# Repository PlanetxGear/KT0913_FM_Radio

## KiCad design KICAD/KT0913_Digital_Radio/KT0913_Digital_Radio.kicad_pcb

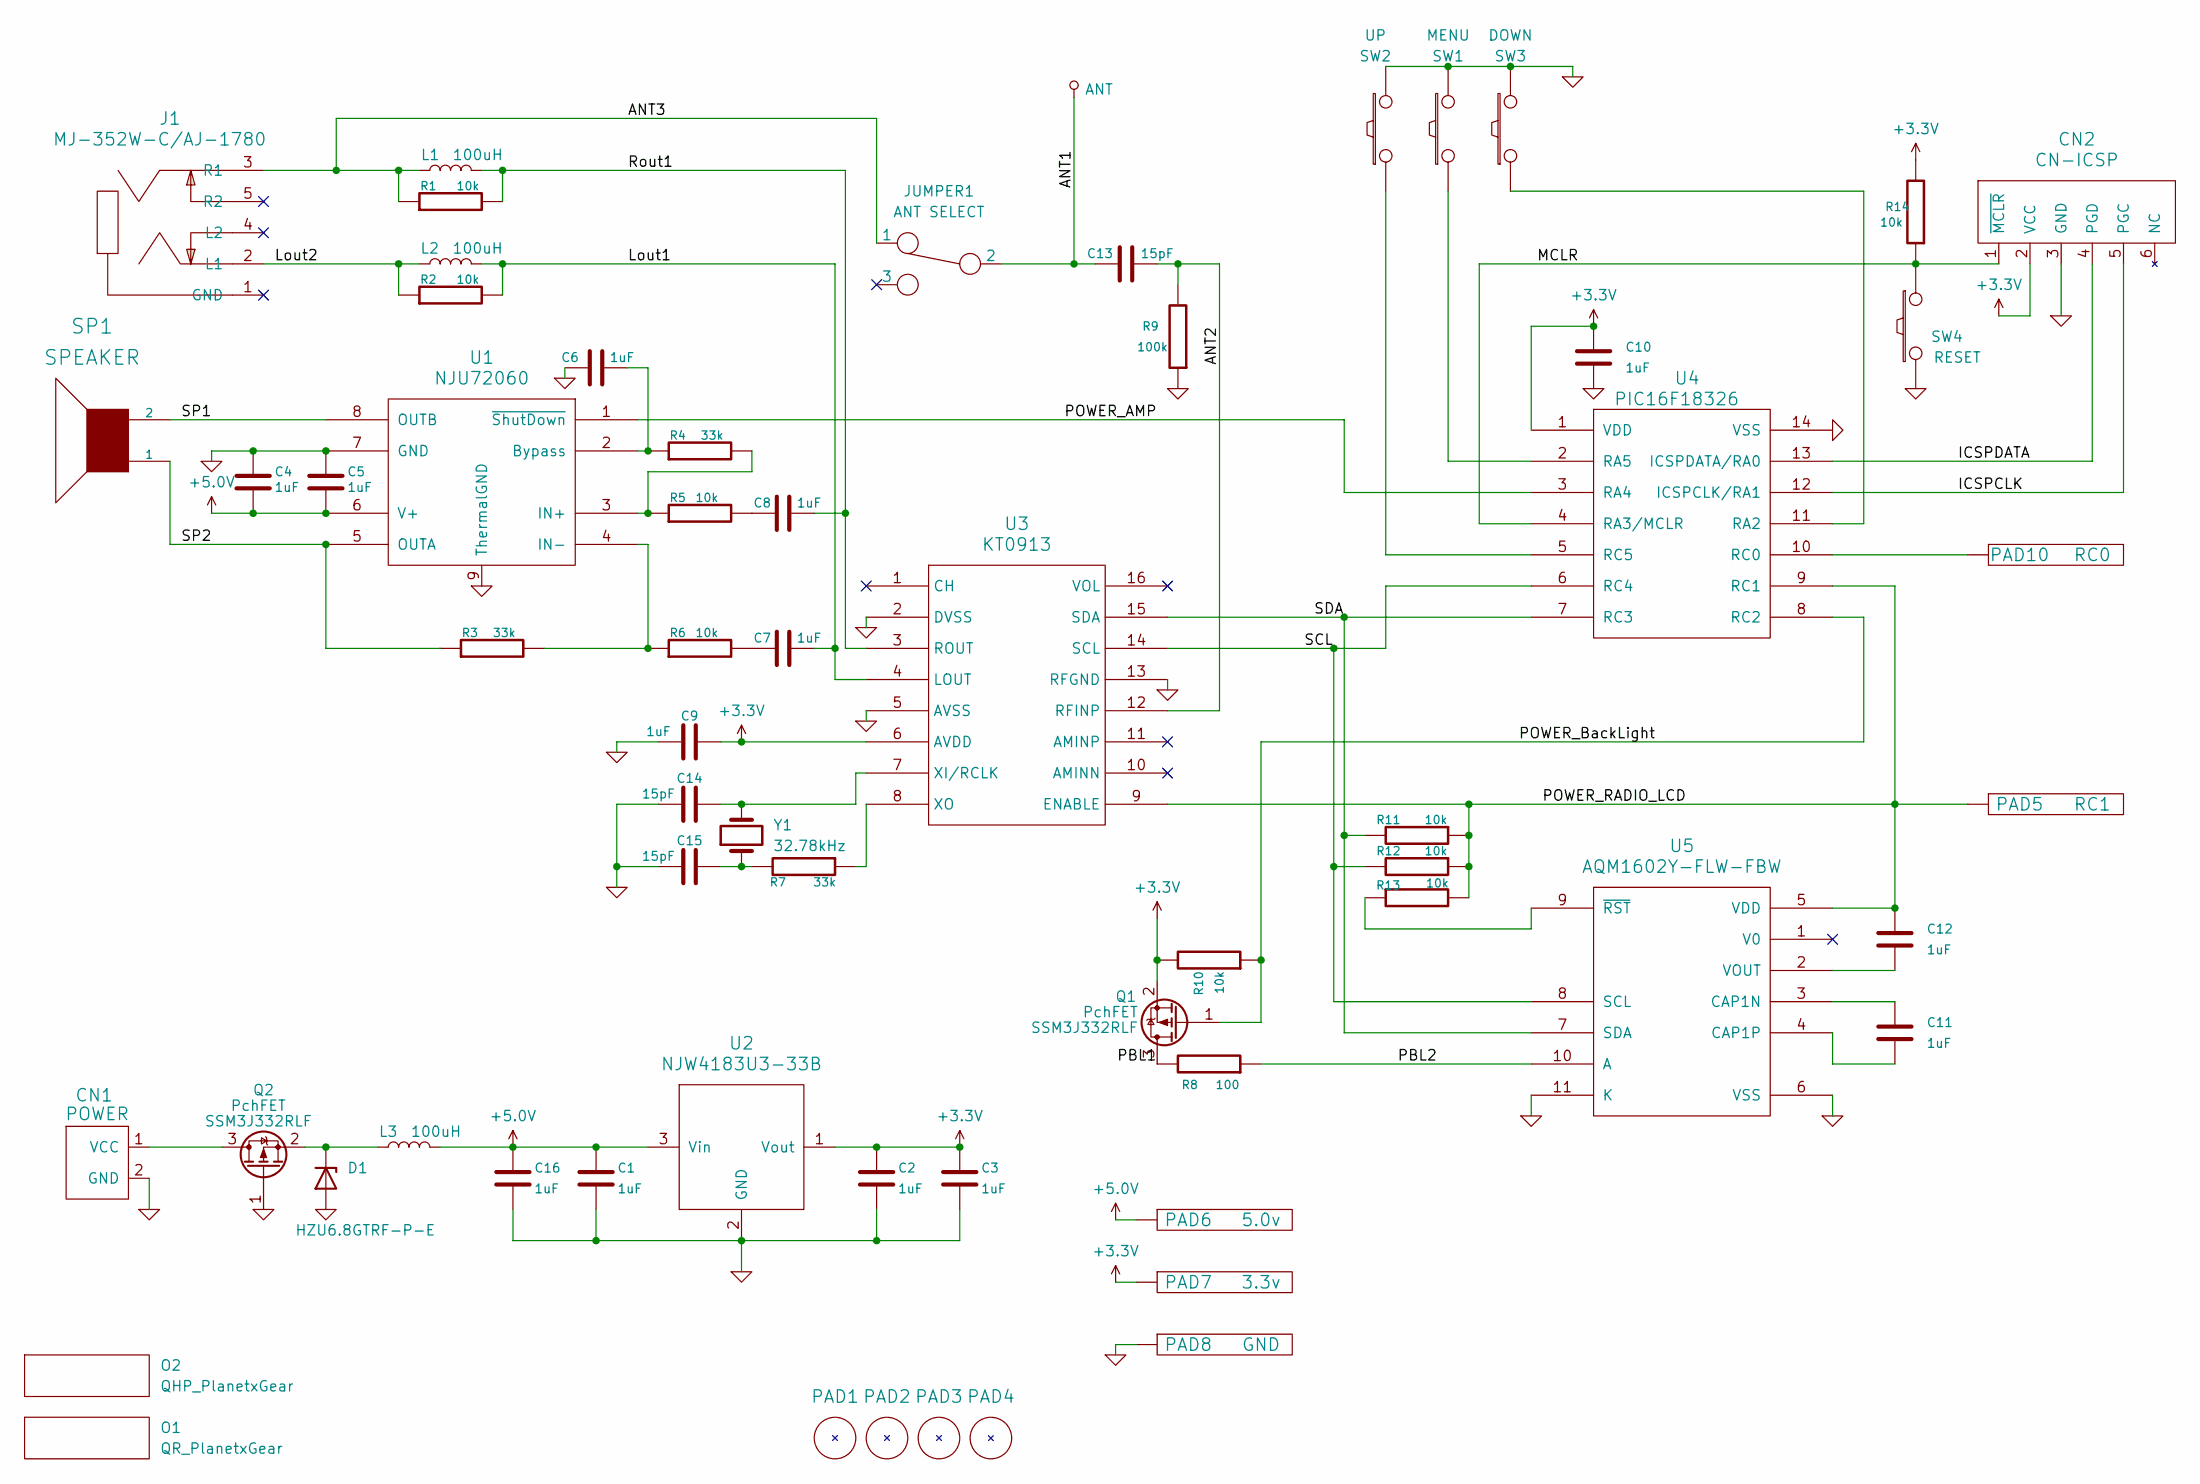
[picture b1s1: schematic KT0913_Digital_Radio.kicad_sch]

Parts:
ANT1: ANT; PAD1mmX2m
C1, C2, C3, C4, C5, C6, C7, C8, C9, C10, C11, C12, C16: 1uF; SMD_0603_1608_MU_HandSolder
C13, C14, C15: 15pF; C2_MU5mm
CN1: POWER; TERMINAL_2P_POWER
CN2: CN-ICSP; PINHEAD1-PICkit_ICSP_Tin
D1: HZU6.8GTRF-P-E; SC-76A
J1: MJ-352W-C/AJ-1780; JACK_EarPhone_MJ-352W-C_R
JUMPER1: ANT SELECT; JUMPER1-3
L1, L2: 100uH; L4_MU9mm
L3: 100uH; L4_MU10mm
O1: QR_PlanetxGear
O2: QHP_PlanetxGear
PAD1, PAD2, PAD3, PAD4: PAD; PAD3mmX5mm
PAD5: RC1; PAD1mmX2m
PAD6: 5.0v; PAD1mmX2m
PAD7: 3.3v; PAD1mmX2m
PAD8: GND; PAD1mmX2m
PAD10: RC0; PAD1mmX2m
Q1, Q2: SSM3J332RLF; SOT-23-3_MU_Handsoldering
R1, R2, R5, R6, R10, R11, R12, R13, R14: 10k; SMD_0603_1608_MU_HandSolder
R3, R4, R7: 33k; R4_MU8mm
R8: 100; R4_MU8mm
R9: 100k; R4_MU8mm
SP1: SPEAKER; TERMINAL_2P
SW1: MENU; SW_PUSH-6mm_AK
SW2: UP; SW_PUSH-6mm_AK
SW3: DOWN; SW_PUSH-6mm_AK
SW4: RESET; SW_PUSH_TVAF06-A020B-R
U1: NJU72060; SOP-8_6x5mm_P1.27mm_EP3.0x4.4mm_ThermalVias
U2: NJW4183U3-33B; SOT-89-3_MU_Handsoldering
U3: KT0913; SSOP-16_MU_3.9x4.9mm_P0.635mm
U4: PIC16F18326; DIP-14_300_MU
U5: AQM1602Y-FLW-FBW; LCD_AQM1602Y-FLW-FBW
Y1: 32.78kHz; X_TAL_VT200

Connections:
+3.3V: C2.1, C3.1, C9.2, C10.1, CN2.2 (VCC), PAD7.1, Q1.2 (S), R10.2, R14.2, U2.1 (Vout), U3.6 (AVDD), U4.1 (VDD)
+5.0V: C1.1, C4.2, C5.2, C16.1, L3.2, PAD6.1, U1.6 (V+), U2.3 (Vin)
/ANT1: ANT1.1 (ANT), C13.2, JUMPER1.2
/ANT2: C13.1, R9.2, U3.12 (RFINP)
/ANT3: J1.3 (R1), JUMPER1.1, L1.1, R1.1
/ICSPCLK: CN2.5 (PGC), U4.12 (ICSPCLK/RA1)
/ICSPDATA: CN2.4 (PGD), U4.13 (ICSPDATA/RA0)
/Lout1: C7.1, L2.2, R2.2, U3.4 (LOUT)
/Lout2: J1.2 (L1), L2.1, R2.1
/MCLR: CN2.1 (~MCLR), R14.1, SW4.1, U4.4 (RA3/MCLR)
/PBL1: Q1.3 (D), R8.2
/PBL2: R8.1, U5.10 (A)
/POWER_AMP: U1.1 (~ShutDown), U4.3 (RA4)
/POWER_BackLight: Q1.1 (G), R10.1, U4.8 (RC2)
/POWER_RADIO_LCD: C12.1, PAD5.1, R11.1, R12.1, R13.2, U3.9 (ENABLE), U4.9 (RC1), U5.5 (VDD)
/Rout1: C8.1, L1.2, R1.2, U3.3 (ROUT)
/SCL: R12.2, U3.14 (SCL), U4.6 (RC4), U5.8 (SCL)
/SDA: R11.2, U3.15 (SDA), U4.7 (RC3), U5.7 (SDA)
/SP1: SP1.2, U1.8 (OUTB)
/SP2: R3.1, SP1.1, U1.5 (OUTA)
GND: C1.2, C2.2, C3.2, C4.1, C5.1, C6.2, C9.1, C10.2, C14.1, C15.1, C16.2, CN1.2 (GND), CN2.3 (GND), D1.2 (A), PAD8.1, Q2.1 (G), R9.1, SW1.2, SW2.2, SW3.2, SW4.2, U1.7 (GND), U1.9 (ThermalGND), U2.2 (GND), U3.2 (DVSS), U3.5 (AVSS), U3.13 (RFGND), U4.14 (VSS), U5.6 (VSS), U5.11 (K)
unnamed: C7.2, R6.2
unnamed: C8.2, R5.2
unnamed: C15.2, R7.2, Y1.1
unnamed: CN1.1 (VCC), Q2.3 (D)
unnamed: D1.1 (K), L3.1, Q2.2 (S)
unnamed: PAD10.1, U4.10 (RC0)
unnamed: C6.1, R4.1, U1.2 (Bypass)
unnamed: R4.2, R5.1, U1.3 (IN+)
unnamed: R3.2, R6.1, U1.4 (IN-)
unnamed: C14.2, U3.7 (XI/RCLK), Y1.2
unnamed: R7.1, U3.8 (XO)
unnamed: SW3.1, U4.11 (RA2)
unnamed: SW1.1, U4.2 (RA5)
unnamed: SW2.1, U4.5 (RC5)
unnamed: C11.1, U5.3 (CAP1N)
unnamed: C11.2, U5.4 (CAP1P)
unnamed: C12.2, U5.2 (VOUT)
unnamed: R13.1, U5.9 (~RST)

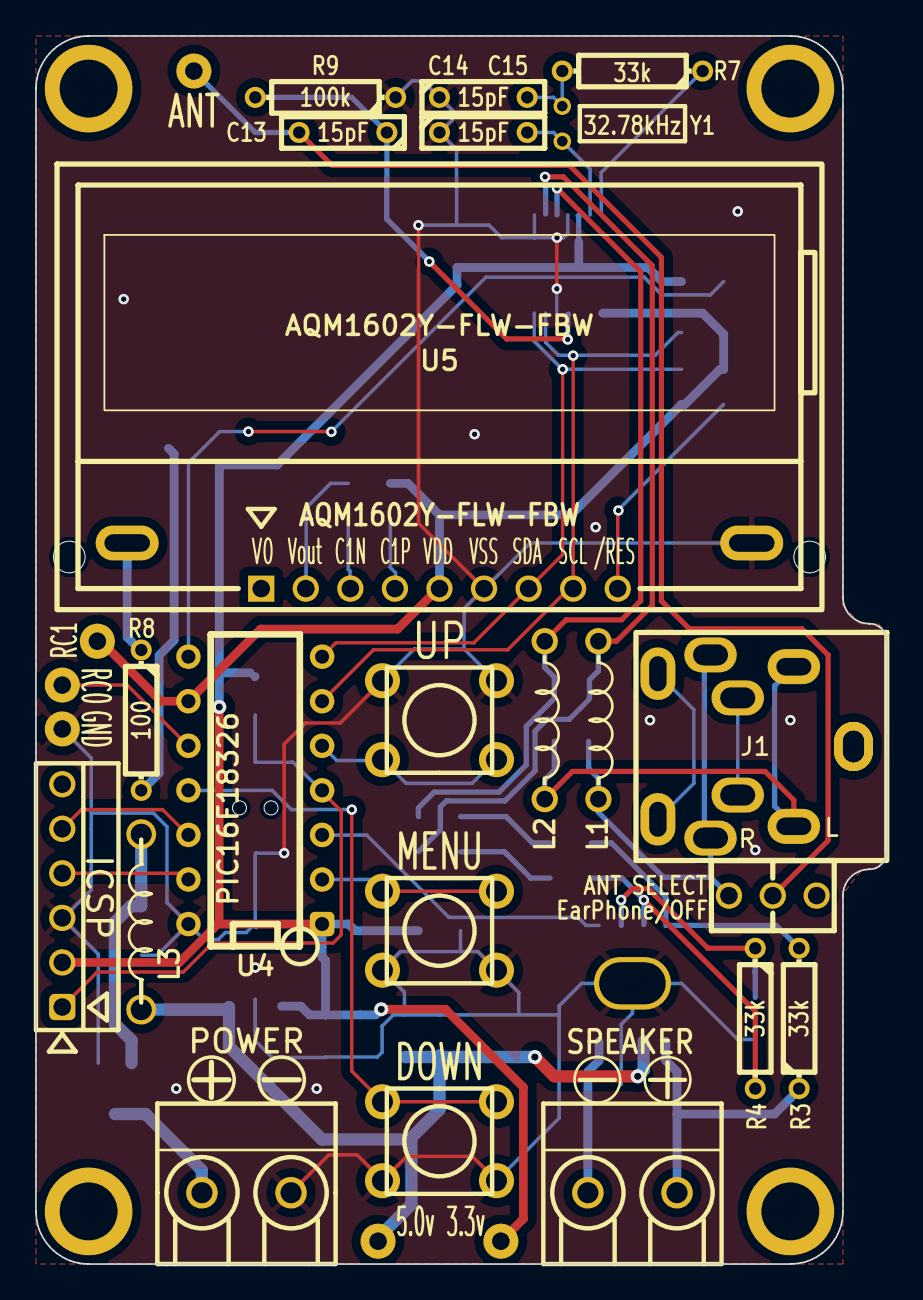
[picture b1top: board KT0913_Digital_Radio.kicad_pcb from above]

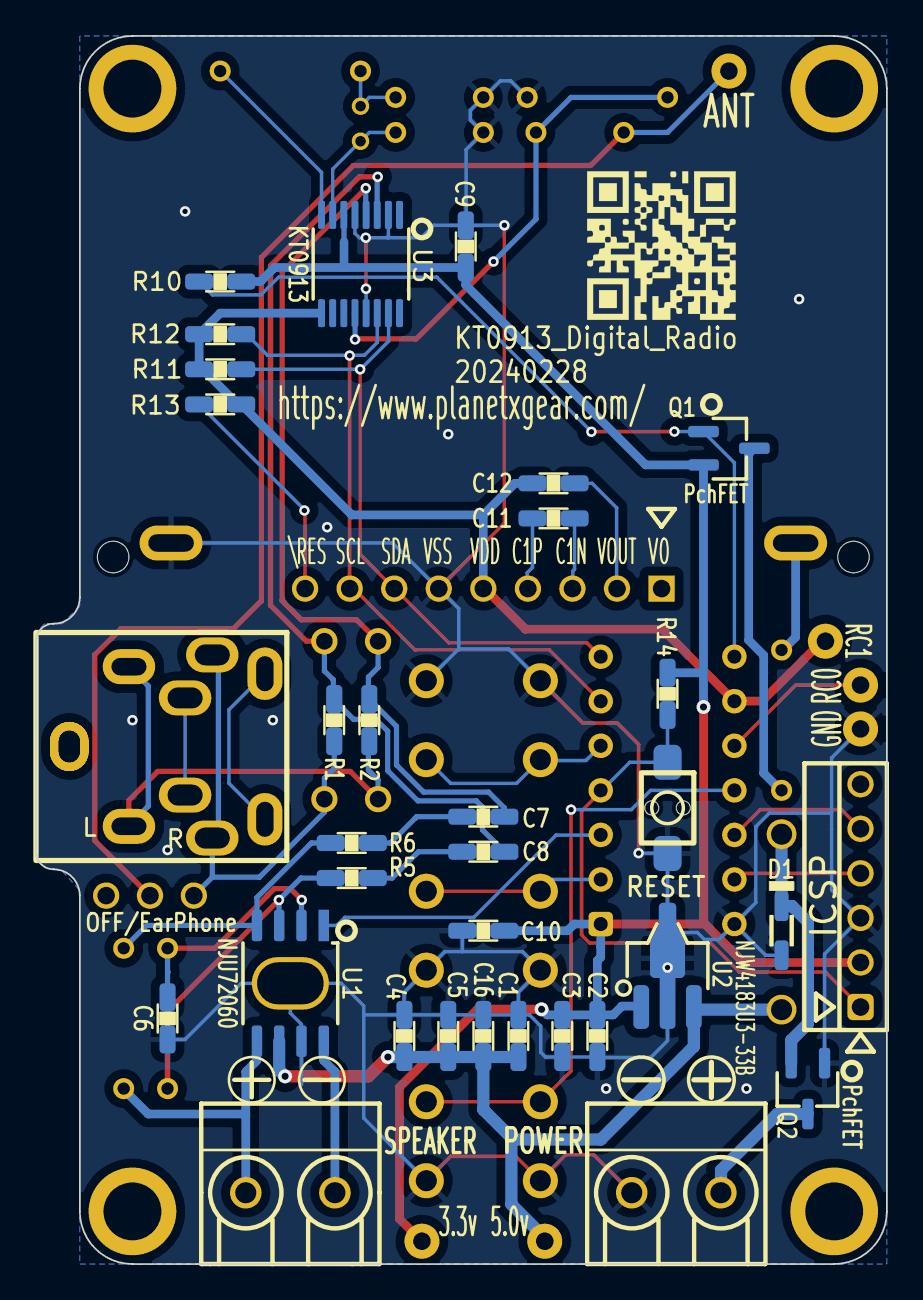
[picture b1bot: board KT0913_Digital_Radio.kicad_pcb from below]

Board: 2 copper layers, 48.5 x 70.0 mm, 63 parts (32 on the bottom side), 39 nets.

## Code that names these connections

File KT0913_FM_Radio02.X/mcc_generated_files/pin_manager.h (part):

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// get/set IO_RA0_NC aliases
#define IO_RA0_NC_TRIS                 TRISAbits.TRISA0
#define IO_RA0_NC_LAT                  LATAbits.LATA0
#define IO_RA0_NC_PORT                 PORTAbits.RA0
#define IO_RA0_NC_WPU                  WPUAbits.WPUA0
#define IO_RA0_NC_OD                   ODCONAbits.ODCA0
#define IO_RA0_NC_ANS                  ANSELAbits.ANSA0
#define IO_RA0_NC_SetHigh()            do { LATAbits.LATA0 = 1; } while(0)
#define IO_RA0_NC_SetLow()             do { LATAbits.LATA0 = 0; } while(0)
#define IO_RA0_NC_Toggle()             do { LATAbits.LATA0 = ~LATAbits.LATA0; } while(0)
#define IO_RA0_NC_GetValue()           PORTAbits.RA0
#define IO_RA0_NC_SetDigitalInput()    do { TRISAbits.TRISA0 = 1; } while(0)
#define IO_RA0_NC_SetDigitalOutput()   do { TRISAbits.TRISA0 = 0; } while(0)
#define IO_RA0_NC_SetPullup()          do { WPUAbits.WPUA0 = 1; } while(0)
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// get/set IO_RA1_NC aliases
#define IO_RA1_NC_TRIS                 TRISAbits.TRISA1
#define IO_RA1_NC_LAT                  LATAbits.LATA1
#define IO_RA1_NC_PORT                 PORTAbits.RA1
#define IO_RA1_NC_WPU                  WPUAbits.WPUA1
#define IO_RA1_NC_OD                   ODCONAbits.ODCA1
#define IO_RA1_NC_ANS                  ANSELAbits.ANSA1
#define IO_RA1_NC_SetHigh()            do { LATAbits.LATA1 = 1; } while(0)
#define IO_RA1_NC_SetLow()             do { LATAbits.LATA1 = 0; } while(0)
#define IO_RA1_NC_Toggle()             do { LATAbits.LATA1 = ~LATAbits.LATA1; } while(0)
#define IO_RA1_NC_GetValue()           PORTAbits.RA1
#define IO_RA1_NC_SetDigitalInput()    do { TRISAbits.TRISA1 = 1; } while(0)
#define IO_RA1_NC_SetDigitalOutput()   do { TRISAbits.TRISA1 = 0; } while(0)
#define IO_RA1_NC_SetPullup()          do { WPUAbits.WPUA1 = 1; } while(0)
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// get/set SW3_down aliases
#define SW3_down_TRIS                 TRISAbits.TRISA2
#define SW3_down_LAT                  LATAbits.LATA2
#define SW3_down_PORT                 PORTAbits.RA2
#define SW3_down_WPU                  WPUAbits.WPUA2
#define SW3_down_OD                   ODCONAbits.ODCA2
#define SW3_down_ANS                  ANSELAbits.ANSA2
#define SW3_down_SetHigh()            do { LATAbits.LATA2 = 1; } while(0)
#define SW3_down_SetLow()             do { LATAbits.LATA2 = 0; } while(0)
#define SW3_down_Toggle()             do { LATAbits.LATA2 = ~LATAbits.LATA2; } while(0)
#define SW3_down_GetValue()           PORTAbits.RA2
#define SW3_down_SetDigitalInput()    do { TRISAbits.TRISA2 = 1; } while(0)
#define SW3_down_SetDigitalOutput()   do { TRISAbits.TRISA2 = 0; } while(0)
#define SW3_down_SetPullup()          do { WPUAbits.WPUA2 = 1; } while(0)
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// get/set POWER_AMP aliases
#define POWER_AMP_TRIS                 TRISAbits.TRISA4
#define POWER_AMP_LAT                  LATAbits.LATA4
#define POWER_AMP_PORT                 PORTAbits.RA4
#define POWER_AMP_WPU                  WPUAbits.WPUA4
#define POWER_AMP_OD                   ODCONAbits.ODCA4
#define POWER_AMP_ANS                  ANSELAbits.ANSA4
#define POWER_AMP_SetHigh()            do { LATAbits.LATA4 = 1; } while(0)
#define POWER_AMP_SetLow()             do { LATAbits.LATA4 = 0; } while(0)
#define POWER_AMP_Toggle()             do { LATAbits.LATA4 = ~LATAbits.LATA4; } while(0)
#define POWER_AMP_GetValue()           PORTAbits.RA4
#define POWER_AMP_SetDigitalInput()    do { TRISAbits.TRISA4 = 1; } while(0)
#define POWER_AMP_SetDigitalOutput()   do { TRISAbits.TRISA4 = 0; } while(0)
#define POWER_AMP_SetPullup()          do { WPUAbits.WPUA4 = 1; } while(0)
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// get/set SW1_menu aliases
#define SW1_menu_TRIS                 TRISAbits.TRISA5
#define SW1_menu_LAT                  LATAbits.LATA5
#define SW1_menu_PORT                 PORTAbits.RA5
#define SW1_menu_WPU                  WPUAbits.WPUA5
#define SW1_menu_OD                   ODCONAbits.ODCA5
#define SW1_menu_ANS                  ANSELAbits.ANSA5
#define SW1_menu_SetHigh()            do { LATAbits.LATA5 = 1; } while(0)
#define SW1_menu_SetLow()             do { LATAbits.LATA5 = 0; } while(0)
#define SW1_menu_Toggle()             do { LATAbits.LATA5 = ~LATAbits.LATA5; } while(0)
#define SW1_menu_GetValue()           PORTAbits.RA5
#define SW1_menu_SetDigitalInput()    do { TRISAbits.TRISA5 = 1; } while(0)
#define SW1_menu_SetDigitalOutput()   do { TRISAbits.TRISA5 = 0; } while(0)
#define SW1_menu_SetPullup()          do { WPUAbits.WPUA5 = 1; } while(0)
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// get/set IO_RC0_NC aliases
#define IO_RC0_NC_TRIS                 TRISCbits.TRISC0
#define IO_RC0_NC_LAT                  LATCbits.LATC0
#define IO_RC0_NC_PORT                 PORTCbits.RC0
#define IO_RC0_NC_WPU                  WPUCbits.WPUC0
#define IO_RC0_NC_OD                   ODCONCbits.ODCC0
#define IO_RC0_NC_ANS                  ANSELCbits.ANSC0
#define IO_RC0_NC_SetHigh()            do { LATCbits.LATC0 = 1; } while(0)
#define IO_RC0_NC_SetLow()             do { LATCbits.LATC0 = 0; } while(0)
#define IO_RC0_NC_Toggle()             do { LATCbits.LATC0 = ~LATCbits.LATC0; } while(0)
#define IO_RC0_NC_GetValue()           PORTCbits.RC0
#define IO_RC0_NC_SetDigitalInput()    do { TRISCbits.TRISC0 = 1; } while(0)
#define IO_RC0_NC_SetDigitalOutput()   do { TRISCbits.TRISC0 = 0; } while(0)
#define IO_RC0_NC_SetPullup()          do { WPUCbits.WPUC0 = 1; } while(0)
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// get/set POWER_RADIO_LCD aliases
#define POWER_RADIO_LCD_TRIS                 TRISCbits.TRISC1
#define POWER_RADIO_LCD_LAT                  LATCbits.LATC1
#define POWER_RADIO_LCD_PORT                 PORTCbits.RC1
#define POWER_RADIO_LCD_WPU                  WPUCbits.WPUC1
#define POWER_RADIO_LCD_OD                   ODCONCbits.ODCC1
#define POWER_RADIO_LCD_ANS                  ANSELCbits.ANSC1
#define POWER_RADIO_LCD_SetHigh()            do { LATCbits.LATC1 = 1; } while(0)
#define POWER_RADIO_LCD_SetLow()             do { LATCbits.LATC1 = 0; } while(0)
#define POWER_RADIO_LCD_Toggle()             do { LATCbits.LATC1 = ~LATCbits.LATC1; } while(0)
#define POWER_RADIO_LCD_GetValue()           PORTCbits.RC1
#define POWER_RADIO_LCD_SetDigitalInput()    do { TRISCbits.TRISC1 = 1; } while(0)
#define POWER_RADIO_LCD_SetDigitalOutput()   do { TRISCbits.TRISC1 = 0; } while(0)
#define POWER_RADIO_LCD_SetPullup()          do { WPUCbits.WPUC1 = 1; } while(0)
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// get/set POWER_BACKLIGHT aliases
#define POWER_BACKLIGHT_TRIS                 TRISCbits.TRISC2
#define POWER_BACKLIGHT_LAT                  LATCbits.LATC2
#define POWER_BACKLIGHT_PORT                 PORTCbits.RC2
#define POWER_BACKLIGHT_WPU                  WPUCbits.WPUC2
#define POWER_BACKLIGHT_OD                   ODCONCbits.ODCC2
#define POWER_BACKLIGHT_ANS                  ANSELCbits.ANSC2
#define POWER_BACKLIGHT_SetHigh()            do { LATCbits.LATC2 = 1; } while(0)
#define POWER_BACKLIGHT_SetLow()             do { LATCbits.LATC2 = 0; } while(0)
#define POWER_BACKLIGHT_Toggle()             do { LATCbits.LATC2 = ~LATCbits.LATC2; } while(0)
#define POWER_BACKLIGHT_GetValue()           PORTCbits.RC2
#define POWER_BACKLIGHT_SetDigitalInput()    do { TRISCbits.TRISC2 = 1; } while(0)
#define POWER_BACKLIGHT_SetDigitalOutput()   do { TRISCbits.TRISC2 = 0; } while(0)
#define POWER_BACKLIGHT_SetPullup()          do { WPUCbits.WPUC2 = 1; } while(0)
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#define RC3_SetHigh()            do { LATCbits.LATC3 = 1; } while(0)
#define RC3_SetLow()             do { LATCbits.LATC3 = 0; } while(0)
#define RC3_Toggle()             do { LATCbits.LATC3 = ~LATCbits.LATC3; } while(0)
#define RC3_GetValue()              PORTCbits.RC3
#define RC3_SetDigitalInput()    do { TRISCbits.TRISC3 = 1; } while(0)
#define RC3_SetDigitalOutput()   do { TRISCbits.TRISC3 = 0; } while(0)
#define RC3_SetPullup()             do { WPUCbits.WPUC3 = 1; } while(0)
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#define RC4_SetHigh()            do { LATCbits.LATC4 = 1; } while(0)
#define RC4_SetLow()             do { LATCbits.LATC4 = 0; } while(0)
#define RC4_Toggle()             do { LATCbits.LATC4 = ~LATCbits.LATC4; } while(0)
#define RC4_GetValue()              PORTCbits.RC4
#define RC4_SetDigitalInput()    do { TRISCbits.TRISC4 = 1; } while(0)
#define RC4_SetDigitalOutput()   do { TRISCbits.TRISC4 = 0; } while(0)
#define RC4_SetPullup()             do { WPUCbits.WPUC4 = 1; } while(0)
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// get/set SW2_up aliases
#define SW2_up_TRIS                 TRISCbits.TRISC5
#define SW2_up_LAT                  LATCbits.LATC5
#define SW2_up_PORT                 PORTCbits.RC5
#define SW2_up_WPU                  WPUCbits.WPUC5
#define SW2_up_OD                   ODCONCbits.ODCC5
#define SW2_up_ANS                  ANSELCbits.ANSC5
#define SW2_up_SetHigh()            do { LATCbits.LATC5 = 1; } while(0)
#define SW2_up_SetLow()             do { LATCbits.LATC5 = 0; } while(0)
#define SW2_up_Toggle()             do { LATCbits.LATC5 = ~LATCbits.LATC5; } while(0)
#define SW2_up_GetValue()           PORTCbits.RC5
#define SW2_up_SetDigitalInput()    do { TRISCbits.TRISC5 = 1; } while(0)
#define SW2_up_SetDigitalOutput()   do { TRISCbits.TRISC5 = 0; } while(0)
#define SW2_up_SetPullup()          do { WPUCbits.WPUC5 = 1; } while(0)
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

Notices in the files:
KT0913_FM_Radio02.X/mcc_generated_files/pin_manager.h:
(c) 2018 Microchip Technology Inc. and its subsidiaries.
